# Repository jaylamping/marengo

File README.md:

# Marengo

> **Read first (2026-11-08):** the robot is now **Roark** and its software is being rebuilt as a fresh, lean stack in its own repo, [jaylamping/roark](https://github.com/jaylamping/roark). This repo is the hardware repo and the read-only reference for the legacy software. Start with
> [roark/TENETS.md](https://github.com/jaylamping/roark/blob/main/TENETS.md) and [roark/PLAN.md](https://github.com/jaylamping/roark/blob/main/PLAN.md). The
> tenets override everything below and every ADR. The existing crates (Davout, Berthier, Chappe, robstride, marengo-pi and the
> rest) are **legacy**: don't extend them, fix their tests or copy their patterns; they are deleted once the new stack passes
> (see [RECONCILIATION.md](review/sw-foundation-20261108/RECONCILIATION.md)).

Returning to the project: start with [docs/status.md](docs/status.md) for where things stand (bench checkpoint, open issues, open decisions, next steps), then [docs/roadmap.md](docs/roadmap.md).

One repo for a personal, full-size walking humanoid in the Unitree G1 class (1524 mm, 23 DOF, Robstride actuators): CAD manifests, wiring, URDF, the Rust runtime, and the operator UI. The live hardware today is the right 5-DOF arm on the bench, the deliberate first slice of the full body. SolidWorks and the harness docs define joints, frames, and limits. Control, safety, planning, and the operator UI read that same definition. When the robot changes in CAD, software should change with it.

## Naming

| Name | Role |
|------|------|
| Marengo | The robot (mechanical + electrical design, URDF, runtime) |
| Armée | Rust workspace: shared types, kinematics, crates |
| Chappe | Message bus between processes |
| Berthier | Realtime control |
| Davout | Safety supervision |
| Consul | Web frontend |
| Talleyrand, Fouché | Planner and Jetson vision/LLM: not built; the scaffolds were removed (2026-10-03 crate audit), [ADR 0014](docs/decisions/0014-jetson-perception-semantic-motion.md) holds the design |

Infrastructure crates and bins use `marengo-*` names.

Wire schemas live in [`proto/`](proto/). More context: [docs/architecture.md](docs/architecture.md), [docs/roadmap.md](docs/roadmap.md) (full humanoid milestones), [ADRs](docs/decisions/README.md), and [AGENTS.md](AGENTS.md) (detailed contributor/agent guide).

## Repository layout

```
marengo/
├── Cargo.toml              # Armée workspace root
├── proto/                  # Protobuf wire types
├── cad/                  # SolidWorks tree (local only); manifests tracked for MCP
│   └── manifests/        # MCP conventions + vendor registry (JSON)
├── hardware/             # Electrical, prints, BOM, hardware docs
│   ├── electrical/       # PDB, harness, CAN docs
│   ├── prints/             # STLs + slicer notes
│   ├── bom/                # Master BOM
│   └── docs/               # Kinematics, assembly, hardware ADRs
├── assets/                 # Exported from hardware, used by software
│   ├── urdf/marengo.urdf   # Master URDF (right arm today, from CAD)
│   ├── mjcf/marengo.xml    # MuJoCo model mirroring the URDF
│   └── meshes/             # visual/ + collision/ (not exported yet)
├── crates/                 # Armée libraries (each has a README)
├── bins/                   # Pi runtimes and dev tools
├── consul/                 # Frontend (Vite + React + TS)
├── tools/                  # Pi bench MCP, research MCP, limit sync
├── sim/                    # MuJoCo smoke tests
├── models/                 # ONNX policies (Git LFS; none yet)
├── config/                 # robot.yaml, motors.yaml, control.yaml, homing.yaml
├── docs/                   # Status, roadmap, architecture, safety, ADRs, commissioning, reviews
└── scripts/                # URDF export, deploy helpers
```

ONNX policies use Git LFS when present. See [.gitattributes](.gitattributes). CAD binaries are local-only — [cad/README.md](cad/README.md).

## Software

### Crates (`crates/`)

| Crate | Role |
|-------|------|
| `berthier` | 200 Hz control loop: trajectories, τ_g, position law, fuses |
| `davout` | Safety supervisor and the only path to the motors: reference/enable sequencing, limits, caps, watchdog, joint↔motor transform |
| `robstride` | Robstride CAN driver (MIT, lifecycle, parameters) |
| `chappe` | Topic bus (protobuf envelopes) and Unix-socket IPC |
| `armee-proto` | Generated protobuf types |
| `armee-kinematics` | URDF limits and velocity-scaled envelope |
| `armee-dynamics` | Gravity torques from URDF; calibration fits |
| `marengo-config` | Typed YAML config, atomic profile writes |
| `marengo-store` | SQLite log/session store |
| `marengo-candump` | candump parse, summary, Robstride enrichment |
| `marengo-deploy` | Pi self-update and deployed-version logic |
| `marengo-host-metrics` | Linux host metrics for Chappe |
| `marengo-imu` | BNO085 IMU driver (SHTP over I2C) |
| `marengo-support` | Shared tracing init |
| `sim-harness` | URDF↔MJCF parity and sim test helpers |

Each crate's boundary is documented at the top of its `src/lib.rs`; READMEs exist for the core crates.

### Binaries (`bins/`)

| Binary | Host | Purpose |
|--------|------|---------|
| `marengo-pi` | Raspberry Pi | Control loop, CAN, Chappe, stdin REPL |
| `marengo-gateway` | Raspberry Pi | HTTP + WebTransport for Consul, log store |
| `motor-repl` | Pi (bench) | `status`, `disable`, `set-zero`, `protocol-inspect`, `gravity-preview` |
| `marengo-log-cli` | Pi / dev | Log archive, candump, `firmware-timing`, `gravity-fit` |
| `marengo-limit-sync` | Dev | Apply a Durable Set Limits patch to a local checkout |
| `imu-probe` | Pi | BNO085 quaternion probe |

### Frontend

[consul/](consul/) is the operator UI: live telemetry, the Hardware page (master URDF/YAML, Set Limits, Set Zero, readiness), testing panels and a URDF viewer.

### Tools

[`tools/marengo-pi-mcp`](tools/marengo-pi-mcp/README.md) drives the bench from an editor (deploy, logs, candump, calibration, motion suite, enable soak). `tools/marengo-research-mcp` is a research helper.

## Hardware workflow

1. Design in SolidWorks under the local `cad/` tree on the Windows PC (assemblies: `marengo.SLDASM`, sub-assemblies per limb).
2. Document limits and frames in [hardware/docs/kinematics.md](hardware/docs/kinematics.md).
3. Export URDF and meshes: `./scripts/export-urdf.sh` → `assets/`.
4. Wire and CAN: [hardware/electrical/wiring/](hardware/electrical/wiring/).

Vendor CAD (Robstride, extrusions) lives under the local `cad/vendor/`; [cad/manifests/vendor-assets.json](cad/manifests/vendor-assets.json) tracks it.

## Build

Windows development and local CAD live at `J:\code\marengo`; macOS uses a host checkout of the same repository. Docker runs the full Linux workspace checks. Start with [Windows and macOS development](docs/windows-macos-development.md) and [onboarding](docs/onboarding.md).

```bash
docker compose build dev
just check
```

Native host setup is optional ([docs/dev-setup.md](docs/dev-setup.md)). Rust conventions for contributors and agents: [docs/rust-patterns.md](docs/rust-patterns.md), [AGENTS.md](AGENTS.md).

Deploy: MCP `pi_sync_main` (preferred), or `scripts/deploy-pi.sh` / `just deploy-pi-docker`. systemd units: `scripts/systemd/`.

## CI

GitHub Actions runs `scripts/check.sh` in the dev image, plus `sim`, `vcan` and `build-image` jobs ([.github/workflows/ci.yml](.github/workflows/ci.yml)).

## License

MIT OR Apache-2.0. See [LICENSE-MIT](LICENSE-MIT) and [LICENSE-APACHE](LICENSE-APACHE).

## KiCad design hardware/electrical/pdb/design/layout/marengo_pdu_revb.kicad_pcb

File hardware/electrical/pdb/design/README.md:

# Power board rev A: design sketch

2026-11-06. First design pass after the architecture plan ([`../PLAN.md`](../PLAN.md)). **Sketch, not a schematic.** It picks a
part for every block, does the calculations that size them, fixes the sheet structure and the HP-to-LP signal list, and
places everything to scale ([`FLOORPLAN.png`](FLOORPLAN.png)). Every part number is **verify** until checked against its
current datasheet and stock at JLCPCB or Digi-Key during schematic capture. Tool: KiCad 10 (project stub in
[`../../schematics/marengo_pdu/`](../../schematics/marengo_pdu/)).

Decided inputs: leg-ready ratings, 80 A continuous / 150 A for 100 ms on the main path (Joey 07:28Z); BMS on the board,
high-side; regen to the pack first, clamp as backup (Joey 08:58Z); HP + LP boards plus a Pi power stub, no XT breakouts.

## 1. Boards in rev A

| Board | Size | Stack-up | Content |
| --- | --- | --- | --- |
| HP (high power) | 100 × 95 mm | 4 layers, 2 oz outer and inner (verify the fab's heavy-copper option and price) | pack in, pack sense connector, BMS AFE, shunt, BMS FET banks, charge port, E-stop banks, VMOT bulk, regen clamp, 6 port channels, port fuses and connectors, fast current amps |
| LP (low power) | 100 × 53 mm | 6 layers, 1 oz | supervisor, 2 CAN bridges, USB hub, 6 CAN transceivers, 12 V and 24 V front ends, point-of-load rails, rail switches and meters, I/O |
| Pi power stub | 30 × 20 mm | 2 layers | 12 V → 5.1 V 6 A buck at the Pi |
| Pack sense | 40 × 25 mm | 2 layers | 14 tap fuses, 3 NTC, 2 × 10 Micro-Fit (battery thread spec) |

## 1a. No plugs on the boards: everything leaves on pigtails (frame check 09:16Z)

The frame thread measured the plug room around the carrier (main 733b9d0): 13.6 mm above the HP top edge before the shared
front rail and shelf plate, 8.5 mm in front, the side edges blocked except a 10 mm band at Z 40 to 50, and 35 mm below the LP
bottom edge. No XT plug fits on the HP board. So rev A puts **no high-current connector on either board**:

- **High-current exits are ring-lug pigtails on low-profile threaded board terminals** (Würth REDCUBE-class M4 press-fit or SMT
  terminals, about 5 to 8 mm tall, 80 A class, verify). Serviceable with a screwdriver, no solder joint carrying the current,
  and the cable leaves flat along the board.
- **Pack power and pack sense mate at the back, at the D2 door,** not at the board. The HP top edge carries a 10 AWG pair and the
  sense harness over the pack's top edge (8.6 mm headroom, fine for cable) to the pack's rear top corner, where they meet the
  pack's XT90S and the battery thread's sense board (pack rear face, X 5 to 45, Y 318 to 343). Unplug at the door, slide the
  pack out: no reaching into the torso, and no shelf cutout needed. Battery thread (09:18Z): the pack's XT90S pigtail is about 60 mm of
  10 AWG from the fuse, and both pack-side connectors sit in a printed holder on the case; board-side leads reach that holder with
  about 30 mm of slack.
- **Arm ports:** pigtails from the HP top corners run up the front corners with the trunk; the arm trunk's first XT30(2+2) joint
  becomes an inline connector on that run. Agreed with the trunk thread (09:18Z): about 250 mm of 16 AWG or heavier plus the
  CAN pair, XT30(2+2) **female on the pigtail** (live side), joint at the frame step corner around Y 360 to 380, 80 to 100 mm
  short of the pitch RS03's top-rear flat, reachable through a removable shell panel, 30 mm of slack at the joint.
- **Waist, aux, leg ports and the charge input:** pigtails leave the HP side edges in the open Z 40 to 50 band and drop past
  the LP board to inline connectors below Y 190 (35 mm of room), or straight to the shell charge port. The leg pigtails are
  fitted when the legs exist.
- **LP bottom edge** carries the small connectors (fans, rail outputs, USB, E-stop loop, sensors), mating downward.
- The floorplan's connector boxes now read as terminal pads; the layout gate re-draws them as such.
- Cable paths reserved by the frame thread (main e1be5af, item 27): over-the-pack run X −35 to 30, Y 345 to 353.6; front-corner
  trunks X ±47 to 55, Z 62 to 70; side drops |X| 50 to 55, Z 40 to 50, Y 160 to 300; LV up-run X 33 to 45, Z 50 to 60, Y 340 to 376
  (12 V, USB, CAN, fan leads to the upper bay). **Layout constraint:** HP top-edge ring lugs and the 10 AWG bend stay inside
  Y 340 to 353.6, Z 43.5 to 60, so the terminals sit flat with the lug pointing up and the cable turning rearward over the pack.

## 2. High-power board

### 2.1 Main path parts

| Block | Part (verify) | Qty | Why |
| --- | --- | --- | --- |
| Pack input | 2 × M4 threaded board terminals + 10 AWG ring-lug pigtail to an XT90 at the pack's rear top corner (section 1a) | 1 | the board's rear face sits 3.5 mm off the pack lid, so nothing mounts there |
| Pack sense | low-profile locking board header (JST GH or Micro-Fit vertical, to fit 13.6 mm) + harness to the pack sense board's 2 × 10 at the rear | 1 | 14 taps, 3 NTC, presence loop, spare |
| BMS AFE | TI BQ76952 on the HP board, next to the shunt and FET banks, so the gate drive and Kelvin sense stay short | 1 | 13 cells per datasheet Table 16-3 (cells 1 to 12 on VC0 to VC12, cell 13 on VC15 to VC16, VC13 to VC15 tied to VC12; section 2.2); 3 pack NTCs plus 1 board NTC; DFETOFF from the E-stop loop and the presence loop; I2C to the LP supervisor through the board-to-board connector |
| Charge port | M4 terminals + pigtail to the shell charge port (XT60), reverse-polarity FET, presence divider | 1 | 4 A, CV 53.9 V; joins PACK+ after the BMS FETs (common port) |
| Pack shunt (low side, for the AFE) | 0.25 mΩ 4-terminal, 5 W, 3921 size (Vishay WSLP3921 or Bourns CSS4J-4026 class) | 1 | 80 A → 20 mV, 1.6 W |
| BMS CHG bank, DSG bank (back-to-back) | Infineon IPT015N10N5 (100 V, 1.5 mΩ, TOLL) | 4 + 4 | see 2.2 |
| BMS predischarge FET + resistor | small 100 V P-FET + 100 Ω 3 W | 1 | AFE PDSG pin (datasheet p45: PDSG charges the load, PCHG charges a low battery), charges VSYS bulk before DSG closes |
| E-stop bank A, bank B | IPT015N10N5 | 3 + 3 | single direction, body diodes VMOT → VSYS (PLAN 3.4) |
| E-stop gate drivers | TI TPS4810-Q1 class 100 V smart high-side driver, one per bank, enable from the loop | 2 | hardware path, short-circuit protection built in |
| VMOT bulk | 8 × 220 µF 80 V polymer-hybrid, Ø10 × 12.5 mm, laid flat if needed | 8 | about 1.8 mF, under the 24 mm height |
| VMOT TVS | SMDJ58A class | 2 | fast edges only |
| Regen clamp | comparator + 100 V FET (IPT015N10N5) self-powered from VMOT; external Arcol HS25 10 Ω 25 W aluminium-clad resistor on the front bottom rail, NC thermostat in the E-stop loop | 1 | see 2.3 |

### 2.2 FET bank sizing

- IPT015N10N5: about 1.5 mΩ at 25 °C, about 2.4 mΩ hot (verify). Four in parallel → 0.6 mΩ hot per bank.
- Conduction loss at 80 A continuous: BMS (two banks in series) 2 × 0.6 mΩ × 80² = 7.7 W; E-stop A + B with 3 each
  (0.8 mΩ hot) = 2 × 0.8 mΩ × 80² = 10 W. **At the typical 10 to 30 A it is 0.2 to 1.6 W in total.** 80 A continuous is a
  rating, not a use case; at that level the board needs the fan and the copper pour to spread about 20 W. Thermal check in the
  layout gate.
- Short circuit: the pack can push about 54.6 V / 0.09 Ω ≈ 600 A prospective. AFE SCD at 40 mV on 0.25 mΩ = **160 A, delay set
  to the minimum (about 15 µs, verify)**. In practice the Class T pack fuse, the port eFuses (faster, lower) and the FET pulse
  rating all share this; the schematic gate must show the FET SOA covers 600 A for about 50 µs.
- Superseded at gate 3 by [RATIONALE-log](RATIONALE-log.md) (0.3 mΩ, OCD1 24 mV, OCC 12 mV, SCD 60 mV). AFE thresholds on 0.25 mΩ, corrected against the BQ76952 datasheet SLUSE13B (p22: OCD/OCC in 2 mV steps, OCC delay max
  425 ms): **OCD1 16 mV = 64 A** (hardware comparator, ≤ 425 ms), **OCD3 60 A for 1 s** (current-based, firmware level inside the
  AFE) as the agreed 60 A ceiling, **OCC 12 mV = 48 A at 425 ms** (stays under the P50B's 50 A pack charge limit), **SCD 40 mV =
  160 A** (valid step).
- Cell wiring per datasheet Table 16-3 (p75): cells 1, 2 and 16 must be real, so cells 1 to 12 on VC0 to VC12, cell 13 on
  VC15 to VC16, VC13 to VC15 shorted to VC12 as the table shows. Thermistors: TS1, TS3, CFETOFF and HDQ as thermistor inputs,
  TS2 left free for wake from SHUTDOWN (DFETOFF stays on the E-stop loop).

### 2.3 Regen clamp sizing

- Threshold 56.77 V on, 55.77 V off (1 V hysteresis, gate 3), self-powered from VMOT.
- Resistor 10 Ω: 56.77² / 10 = 322 W while on, 5.7 A, which matches the host's 5 A braking cap when the pack is full (PLAN
  3.4). The HS25 has no published pulse rating (see below); the supervisor logs on-time and the resistor's NTC, and an NC
  thermostat on its plate opens the E-stop loop in hardware.
- Arm drop for scale: about 15 J, under 0.1 s of clamp on-time.

### 2.4 Port channels

| Item | Arms, waist, aux (4) | Legs (2, unpopulated in rev A) |
| --- | --- | --- |
| Hot-swap controller | TI LM5069 (9 to 80 V, circuit breaker, dV/dt soft start) | LM5069 |
| FET | 1 × IPT015N10N5 | 2 × IPT015N10N5 |
| Sense resistor (LM5069, shared with the meter and fast amp) | 2.5 mΩ, 3 W (1.0 W at 20 A) → 22 A limit | 1.2 mΩ, 5 W (1.9 W at 40 A) → 46 A limit |
| Meter | TI INA228 (85 V, 20-bit, energy registers) on the same shunt | INA228 |
| Fast current | TI INA241 (−5 to 110 V common mode) on the same shunt → LP ADC | INA241 |
| Fuse | 15 A blade, **58 V DC rated** (Littelfuse 997 MINI 58 V class) in a 58 V holder | 40 A, 58 V |
| Load-side clamp | 59 V mini clamp, about 20 W (footprint, may stay unpopulated) | same |
| CAN TVS | NUP2105L class at the connector | same |
| Connector | M4 terminals + CAN header on the board; pigtail to an inline XT30(2+2) | M4 terminals + CAN header; pigtail to inline XT60 + JST GH |

> Port values in this table are superseded: arm, waist, aux now use 3 mΩ, limit 16.2 to 20.5 A, software trip 15 A, 20 A fuse. See [RATIONALE-log.md](RATIONALE-log.md), follow-ups.

The LM5069 current limit is set by a 55 mV (typ, verify) sense threshold: 2.5 mΩ gives 22 A for the 20 A ports, 1.2 mΩ gives
46 A for the 40 A legs. The circuit-breaker timer is set so the electronic trip always beats the blade fuse.

## 3. Low-power board

| Block | Part (verify) | Notes |
| --- | --- | --- |
| Supervisor MCU | ST STM32G0B1 (USB, plenty of I2C, low power) | separate from the CAN bridges |
| CAN bridges | 2 × ST STM32G474 (3 FDCAN each), candleLight/gs_usb firmware | 6 buses |
| USB hub | Microchip USB2514B (4 port) | supervisor + 2 bridges + service port; one USB-C up to the Pi |
| CAN | 6 × TI TCAN1462V-Q1, non-isolated (gate 3 default) | bus pins ±58 V, ±45 V differential |
| 12 V intermediate, 150 W | TI LM5145 (6 to 75 V sync buck controller) + 100 V FETs | from VSYS through the ideal diode |
| 24 V, 75 W | second LM5145 | from VSYS |
| Ideal diode + hold-up | TI LM74700-Q1 + 1 mF at VSYS (rides 10 ms at 90 W down to 20 V) | |
| 7.4 V servo (6 to 8.4 V), 5 A | TI TPS56637 (4.5 to 28 V in, 6 A) | adjustable by resistor |
| 5 V peripheral, 4 A | TPS56637 | |
| 3.3 V peripheral, 2 A | TI TPS62933 | |
| 5 V / 3.3 V clean | TI TPS7A20 LDOs | under 5 mV ripple |
| Spare rail slot, 3 A | TPS62933 footprint, output set by resistor | |
| 3.3 V always-on | TI LMR38010 (4.2 to 80 V in, 1 A) | from VSYS, ahead of everything |
| Rail switches | TI TPS2663 (60 V, 6 A eFuse) per 12 V and 24 V output; TPS22965 class for 5 V and 3.3 V | each switchable by the supervisor |
| Rail meters | INA238 per output (10) | 2 I2C buses, 5 meters each |
| Fan drivers | 3 × 4-pin PWM headers, tach to the supervisor | |
| E-stop loop | 12 V loop supply, opto or comparator inputs, 2 independent enable outputs to the HP gate drivers | no firmware in the enable path |

## 4. Schematic sheet structure (KiCad hierarchy)

```
marengo_pdu (root)
├── HP_power_board
│   ├── pack_input_shunt_afe   (BQ76952 lives on HP)
│   ├── bms_fets_precharge
│   ├── estop_banks
│   ├── vmot_bulk_clamp
│   └── port_channel ×6        (one sheet, instanced; legs DNP)
├── LP_logic_board
│   ├── supervisor_mcu
│   ├── can_bridges_usb_hub
│   ├── can_phy ×6             (instanced)
│   ├── front_end_12v_24v
│   ├── pol_rails
│   ├── rail_switches_meters
│   └── io_fans_estop_loop
├── pi_power_stub
└── pack_sense_board
```

## 5. HP-to-LP board-to-board connector (draft)

> Superseded by the captured pinout: two 2x15 ribbons, J101 and J102 on `HP_power_board.kicad_sch`. Reasons are in [RATIONALE-log.md](RATIONALE-log.md), section HP_power_board top sheet.

One locking 2 × 30 header, 2.0 mm pitch, along the HP bottom edge and the LP top edge. No motor current crosses it.

| Pins | Signal |
| --- | --- |
| 6 | VSYS (to the LP front ends, up to 5 A total) |
| 6 | GND |
| 2 | E-stop enable A, enable B (loop logic on LP → gate drivers on HP) |
| 2 | E-stop bank A and B status (drain-source sense) |
| 2 | VMOT sense, clamp status |
| 6 | port enables |
| 6 | fast current outputs from the INA241s |
| 3 | AFE I2C (SDA, SCL) and AFE ALERT |
| 2 | HP meter I2C (port INA228s, HP NTCs) |
| 2 | AFE DFETOFF (loop) and RST_SHUT |
| 12 | CAN_H / CAN_L for the six ports, from the transceivers on LP to the port connectors on HP |
| 2 | charger present, board present |
| 9 | spare and extra GND between CAN pairs |

## 6. Next

1. Joey installs KiCad 10 on Joey-PC.
2. Schematic capture sheet by sheet, starting with the HP main path and the AFE (the safety-critical core), with the calculation
   notes above carried into the schematic as text.
3. Gate 3 review of the schematic (review recipe), then layout.

## 1b. Frame gate 2 constraints for layout (frame thread 11:23Z, main 8a15651)

- **Stack:** carrier Z 37.5 to 41.5, 6 mm M3 F-F standoffs, PCBs from Z 47.5 (top copper Z 49.1), component ceiling Z 61.5. That
  leaves 12.4 mm above the board; the 10.8 mm hold-up caps keep 1.6 mm. Standoff hole positions are set at layout and sent to
  the frame thread.
- **Corner screw heads:** X ±46.5 to 51, Y 175 to 203 and 325 to 353, Z 55 to 65. Boards stay 100 mm wide. Each outer corner
  (|X| > 46, Y 190 to 203 and Y 325 to 340) is a keep-out for parts taller than 5 mm. The arm-port M4 terminals and their
  upward ring lugs move inboard of |X| 44, clear of the posts at Y 325 to 353.
- **Brake resistor, rev A: Arcol HS25 10 Ω** (frame main 04983bb). It replaces the HS50 to clear the pack's bottom front edge.
  Datasheet maxima: 28.0 wide, 51.0 over the tags, 14.6 tall, holes on 18.3 × 19.8 mm. It sits flat on a 2 mm aluminium plate on
  the front bottom rail's inner face, at |X| ≤ 25.5, Y 154 to 182, Z 33.4 to 48. Arcol publishes no pulse rating, so ask Arcol
  before the leg stage; the 2 Ω leg stage takes a bigger part in the 37 mm rail reserve. Leads go to the LP bottom edge.
  Keep the LP bottom-edge connectors at |X| > 36 or above Y 190. BOM and schematic now carry the HS25.
- **Pigtail bundles, per port, flat:**
  - Arm: 2 × 16 AWG silicone (Ø about 2.9) plus a twisted CAN pair (about Ø2.5), about 8 × 3 mm.
  - Leg: 2 × 12 AWG silicone (Ø about 4) plus CAN, about 10.5 × 4 mm.
  - One arm bundle fits the 5 × 8 mm side band. A leg bundle does not fit at the band's full height, and an arm plus a leg
    together never fit in one cross-section.
  - All ring lugs are booted with heat-shrink.
- **Housing bond:** if the RS03 housings are at GND, the frame becomes GND through the motors and the 1 MΩ || 10 nF bond is
  moot. Meter-check a real RS03 (housing to its GND pin) before layout fixes the bond.

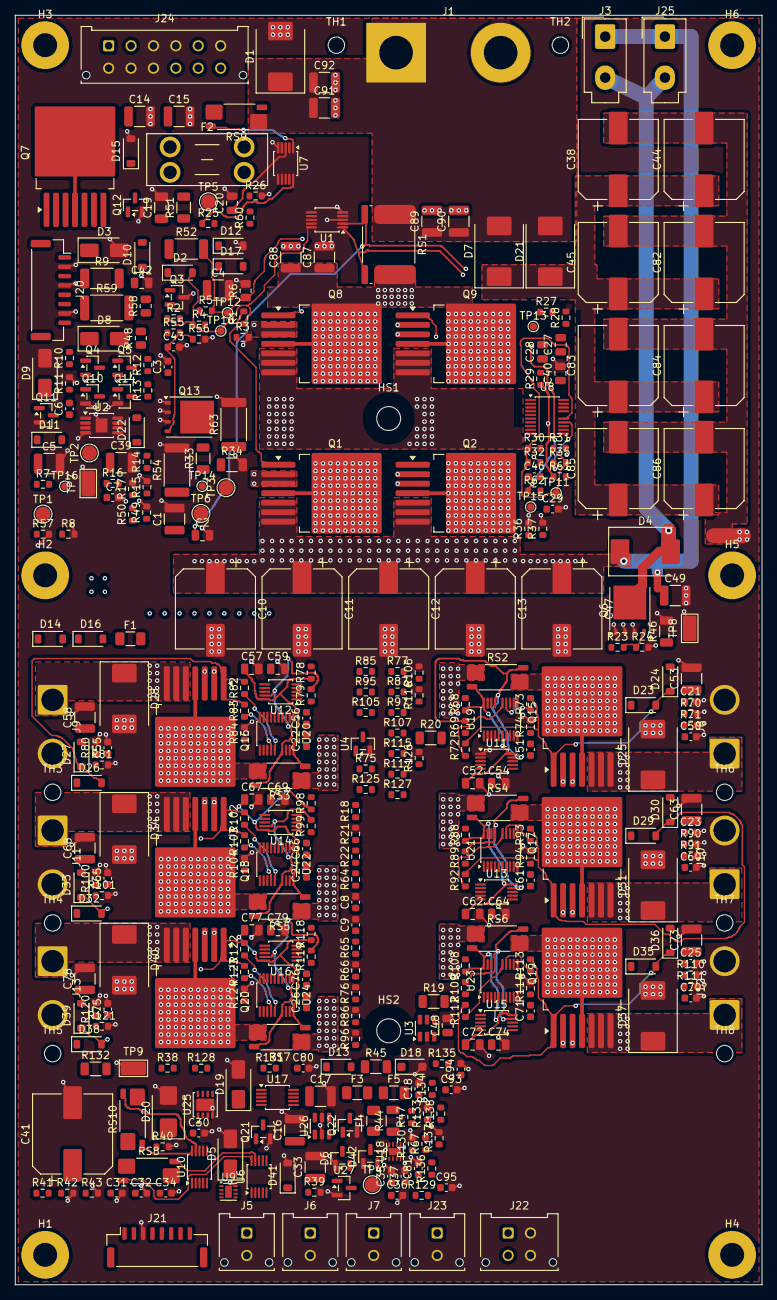
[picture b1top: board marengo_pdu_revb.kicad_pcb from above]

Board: 4 copper layers, 100.0 x 170.0 mm, 387 parts (0 on the bottom side), 201 nets.

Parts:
C1: 1uF 100V X7R soft-term; C_1210_3225Metric
C2, C20: 100nF 100V X7R soft-term; C_0805_2012Metric
C3: 4.7nF C0G; C_0603_1608Metric
C4: 100nF 100V C0G; C_1210_3225Metric
C5: 10uF 50V X7R; C_1210_3225Metric
C6: 2.2nF C0G; C_0603_1608Metric
C7: 10nF 50V X7R; C_0603_1608Metric
C8, C18, C21, C22, C23, C24, C25, C26, C30, C32, C34, C36, C43, C80, C94: 100nF 50V X7R; C_0603_1608Metric
C9: 100pF C0G; C_0603_1608Metric
C10, C11, C12, C13, C38, C44, C45, C47, C82, C83, C84, C85, C86: 47uF 80V EEH-ZC1K470P; CP_Elec_10x10.5
C14, C15, C53, C58, C63, C68, C73, C78: 2.2uF 100V X7R; C_1210_3225Metric
C16, C17, C33: 22uF 25V X7R; C_1210_3225Metric
C19: 220nF C0G; C_1206_3216Metric
C27, C52, C54, C57, C59, C62, C64, C67, C69, C72, C74, C77, C79: 100nF 100V X7R; C_0805_2012Metric
C28: 2.2uF 25V X7R; C_0805_2012Metric
C29: 680pF C0G; C_0603_1608Metric
C31, C35, C81: 3.3nF C0G; C_0603_1608Metric
C37, C95: 1nF 50V X7R; C_0603_1608Metric
C39, C49: 1uF 100V X7R; C_1210_3225Metric
C40: 22nF 100V; C_0805_2012Metric
C41: 330uF 25V EEH-ZA1E331P; CP_Elec_10x10.5
C42: 1uF 50V X7R; C_0805_2012Metric
C46: 1nF C0G; C_0603_1608Metric
C48: 4.7uF 10V X7R; C_0805_2012Metric
C50, C55, C60, C65, C70, C75: 1uF 16V X7R; C_0603_1608Metric
C51, C56, C61, C66, C71, C76, C93: 220nF 25V X7R; C_0603_1608Metric
C87, C88, C89, C90, C91, C92: 4.7uF 100V X7R; C_1210_3225Metric
D1: 5.0SMDJ58A; D_SMC
D2, D10, D11, D22, D23, D26, D29, D32, D35, D38: BAV19W; D_SOD-123
D3, D9: SMAJ15A; D_SMA
D4: MBRS3100T3G; D_SMC
D5, D19: B340A-13-F; D_SMA
D6, D42: BAT54S; SOT-23
D7, D21, D25, D28, D31, D34, D37, D40: SK810L-TP; D_SMC
D8: ES1D; D_SMA
D12, D15: BZT52C12; D_SOD-123
D13, D17: BAT46W; D_SOD-123
D14: BZT52C10; D_SOD-123
D16: BZT52C5V1; D_SOD-123
D18: BZT52H-C68,115; D_SOD-123F
D20: SMBJ15A; D_SMB
D24, D27, D30, D33, D36, D39: BZT52C15; D_SOD-123
D41: BZT52C3V3; D_SOD-123
F1: 250mA 125V 0466.250; Fuse_1206_3216Metric
F2: 20A 58V MINI 0997020.WXN; Fuseholder_Blade_Mini_Keystone_3568
F3, F4: 5A 32V 0466005; Fuse_1206_3216Metric
F5: 2A 32V 0466002; Fuse_1206_3216Metric
H1, H2, H3, H4, H5, H6: MountingHole_3.2mm_M3_Pad
HS1, HS2: MountingHole_3.2mm_M3
J1: Pack: 8 AWG pigtail pair to an XT90 (mat; SolderWire-8AWG_1x02_P14mm_D4.5mm_OD8mm
J3: HS50 A (+X): 1 VBUS, 2 FET drain (Mini-F; Molex_Mini-Fit_Jr_5566-02A_2x01_P4.20mm_Vertical
J5: 12 V to Jetson (fused, block 10c); Molex_Micro-Fit_3.0_43045-0212_2x01_P3.00mm_Vertical
J6: 12 V to Pi 5 V buck (fused, block 10c); Molex_Micro-Fit_3.0_43045-0212_2x01_P3.00mm_Vertical
J7: 12 V to fans (fused, block 10c); Molex_Micro-Fit_3.0_43045-0212_2x01_P3.00mm_Vertical
J8: L arm: 16 AWG pigtail pair, 1 +, 2 retur; SolderWire-2.5sqmm_1x02_P7.2mm_D2.4mm_OD3.6mm
J9: R arm: 16 AWG pigtail pair, 1 +, 2 retur; SolderWire-2.5sqmm_1x02_P7.2mm_D2.4mm_OD3.6mm
J10: waist: 16 AWG pigtail pair, 1 +, 2 retur; SolderWire-2.5sqmm_1x02_P7.2mm_D2.4mm_OD3.6mm
J11: aux: 16 AWG pigtail pair, 1 +, 2 return; SolderWire-2.5sqmm_1x02_P7.2mm_D2.4mm_OD3.6mm
J12: L leg: 14 AWG pigtail pair, 1 +, 2 retur; SolderWire-2.5sqmm_1x02_P7.2mm_D2.4mm_OD3.6mm
J13: R leg: 14 AWG pigtail pair, 1 +, 2 retur; SolderWire-2.5sqmm_1x02_P7.2mm_D2.4mm_OD3.6mm
J20: E-stop: 1 NC out, 2 GND, 3 NC return, 4; JST_GH_SM08B-GHS-TB_1x08-1MP_P1.25mm_Horizontal
J21: Pi: 3V3, SDA, GND, SCL, E-stop pressed (; JST_GH_SM08B-GHS-TB_1x08-1MP_P1.25mm_Horizontal
J22: SPARE_SW, off with the motors (2 x 2, ke; Molex_Micro-Fit_3.0_43045-0412_2x02_P3.00mm_Vertical
J23: SPARE_ON, always on; Molex_Micro-Fit_3.0_43045-0212_2x01_P3.00mm_Vertical
J24: 12 V converter pigtail: 1-2 +VIN, 3-4 -V; Molex_Micro-Fit_3.0_43045-1212_2x06_P3.00mm_Vertical
J25: HS50 B (-X): 1 VBUS, 2 FET drain (Mini-F; Molex_Mini-Fit_Jr_5566-02A_2x01_P4.20mm_Vertical
Q1, Q2, Q7, Q8, Q9, Q15, Q16, Q17, Q18, Q19, Q20: IPB017N10N5LFATMA1; TO-263-7_TabPin4
Q3: MMBTA92LT1G; SOT-23
Q4: MMBT3906; SOT-23
Q5, Q10, Q11, Q14, Q21: MMBT3904; SOT-23
Q6, Q13: BSC040N10NS5ATMA1; TDSON-8-1
Q12, Q22: 2N7002; SOT-23
R1, R2, R23, R25, R31, R32: 10R; R_0603_1608Metric
R3: 34k 1%; R_0603_1608Metric
R4, R12, R66: 1k; R_0603_1608Metric
R5, R75, R85, R95, R105, R115, R125, R131: 22k; R_0603_1608Metric
R6: 33k; R_0805_2012Metric
R7: 464k; R_0603_1608Metric
R8: 49.9k; R_0603_1608Metric
R9: 680R 0.5W; R_2010_5025Metric
R10: 4.7k; R_0603_1608Metric
R11, R14, R16, R17, R27, R67, R76, R86, R96, R106, R116, R126, R129: 10k; R_0603_1608Metric
R13, R24, R28, R37, R38, R41, R50, R55, R65, R71, R72, R77, R81, R82, R87, R91, R92, R97, R101, R102, R107, R111, R112, R117, R121, R122, R127, R130, R137: 100k; R_0603_1608Metric
R15: 1.2k; R_0603_1608Metric
R18, R134: 9.09k; R_0603_1608Metric
R19: 499k 0.1%; R_1206_3216Metric
R20: 604k 0.1%; R_1206_3216Metric
R21: 51.1k 0.1%; R_0603_1608Metric
R22, R64: 9.53M; R_0603_1608Metric
R26: 37.4k 1%; R_0603_1608Metric
R29, R68, R78, R88, R98, R108, R118, R138: 100R; R_0603_1608Metric
R30, R56: 1M; R_0603_1608Metric
R33, R34: 47k 1%; R_1206_3216Metric
R35, R73, R83, R93, R103, R113, R123: 22R; R_0603_1608Metric
R36: 40.2k 1%; R_0603_1608Metric
R39: 68k; R_0603_1608Metric
R40: 499R 1%; R_0603_1608Metric
R42, R47: 33k; R_0603_1608Metric
R43: 1.02k 1%; R_0603_1608Metric
R44: 3.3k; R_1206_3216Metric
R45, R46: 100k; R_1206_3216Metric
R48: 220k; R_0805_2012Metric
R49, R57: 220k; R_0603_1608Metric
R51: 470k; R_1206_3216Metric
R52: 10k 0.75W; R_2010_5025Metric
R53: copper link; NetTie-2_SMD_Pad2.0mm
R54: 2R 2512 pulse-rated 100mJ; R_2512_6332Metric
R58: 47k; R_0805_2012Metric
R59: 22R CRCW251222R0FKEGHP; R_2512_6332Metric
R60: 220R; R_0603_1608Metric
R61, R62: 0R; R_0603_1608Metric
R63: 4.7k 2W; R_2512_6332Metric
R69, R79, R89, R99, R109, R119: 4.64k 1%; R_0603_1608Metric
R70, R80, R90, R100, R110, R120: 20k 1%; R_0603_1608Metric
R74, R84, R94, R104, R114, R124: 10M; R_0603_1608Metric
R128: 2.2k; R_0603_1608Metric
R132: 118k 1%; R_1206_3216Metric
R133, R135: 10k 1%; R_0603_1608Metric
R136: 499k 1%; R_0603_1608Metric
RS1: 0.5mR Bourns CSS4J-4026R-L500F 5W; R_Shunt_Isabellenhuette_BVR4026
RS2, RS3, RS4, RS5, RS6, RS7: 2mR 2512 CSS2H-2512K-2L00F 5W; R_Shunt_Vishay_WSK2512_6332Metric_T1.19mm
RS8: 2mR 2512 Kelvin WSK25122L000FEA; R_Shunt_Vishay_WSK2512_6332Metric_T1.19mm
RS9, RS10: 5mR 2512 Kelvin WSK25125L000FEA; R_Shunt_Vishay_WSK2512_6332Metric_T1.19mm
TH1, TH2, TH3, TH4, TH5, TH6, TH7, TH8: MountingHole_2.2mm_M2
TP1: TP VCTL; TestPoint_Pad_D2.0mm
TP2: TP RUN; TestPoint_Pad_D2.0mm
TP3: TP VBUS; TestPoint_Pad_D2.0mm
TP4: TP +12V; TestPoint_Pad_D2.0mm
TP5: TP BRK_IN; TestPoint_Pad_D2.0mm
TP6: TP MID; TestPoint_Pad_D2.0mm
TP7, TP8, TP9: TP GND; TestPoint_Keystone_5015_Micro_Mini
TP10: TP GATE; TestPoint_Pad_D1.0mm
TP11: TP GATE_A; TestPoint_Pad_D1.0mm
TP12: TP UVLO; TestPoint_Pad_D1.0mm
TP13: TP FLT_A; TestPoint_Pad_D1.0mm
TP14: TP SW_D; TestPoint_Pad_D1.0mm
TP15: TP ABS; TestPoint_Pad_D1.0mm
TP16: TP WDO_N; TestPoint_Pad_D1.0mm
U1: LM5069MMX-1; MSOP-10_3x3mm_P0.5mm
U2: TPS7A4001DGNR; HVSSOP-8-1EP_3x3mm_P0.65mm_EP1.57x1.89mm
U3, U26: TLV1805DBVR; SOT-23-6
U4, U27: LM4040AIM3-2.5; SOT-23
U6, U10, U11, U12, U13, U14, U15, U16, U17: INA237AIDGSR; TSSOP-10_3x3mm_P0.5mm
U7: LM5069MMX-2; MSOP-10_3x3mm_P0.5mm
U8: TPS48100QDGXRQ1; TPS48100_DGX_VSSOP-19
U9, U18: TPS259541DSGR; Texas_DSG0008A_WSON-8-1EP_2x2mm_P0.5mm_EP0.9x1.6mm
U19, U20, U21, U22, U23, U24: TPS48111LQDGXRQ1; TPS48100_DGX_VSSOP-19
U25: TPS3431SDRBR; VSON-8-1EP_3x3mm_P0.65mm_EP1.65x2.4mm

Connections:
/+3V3_PI: C18.1, C21.1, C22.1, C23.1, C24.1, C25.1, C26.1, C30.1, C34.1, D6.2, D13.2, D42.2, J21.1, R67.2, U6.2, U6.6, U10.1, U10.6, U11.6, U12.2, U12.6, U13.6, U14.6, U15.1, U15.6, U16.1, U16.2, U16.6, U17.6
/+12V: C32.1, C36.1, C41.1, D20.1, F3.1, F4.1, F5.1, R41.1, RS8.4, TP4.1, U6.8, U9.3, U9.4, U18.3, U18.4
/+12V_FAN: F5.2, J7.1
/+12V_JET: F3.2, J5.1
/+12V_PI: F4.2, J6.1
/+12V_RAW: C16.1, C17.1, J24.10, J24.11, J24.12, RS8.1
/ABS: C38.1, C44.1, C45.1, C82.1, C83.1, C84.1, C85.1, C86.1, D7.1, D21.1, R46.1, TP15.1
/ABS_N: C38.2, C44.2, C45.2, C82.2, C83.2, C84.2, C85.2, C86.2, Q13.5, R53.1, R54.1
/BAT: C1.1, C89.1, C90.1, C91.1, C92.1, D1.1, D7.2, D21.2, F1.1, J1.1, RS1.1, RS9.1
/BAT_CTL: C39.1, D8.1, U2.5, U2.8
/BAT_F: F1.2, R59.1
/BAT_R: D8.2, R59.2
/BRK_D: Q7.4, RS9.4
/BRK_F: F2.2, J24.1, J24.2
/BRK_G1: Q7.1, R25.2
/BRK_GATE: R25.1, U7.10
/BRK_IN: C14.1, C15.1, F2.1, Q7.2, Q7.3, Q7.5, Q7.6, Q7.7, R51.1, R132.1, TP5.1, U7.9
/BRK_ON: J24.5, R60.2
/BRK_OND: Q12.3, R60.1
/BRK_P: R26.1, U7.7
/BRK_PG: D15.1, Q12.1, R51.2, U7.8
/BRK_T: C19.1, U7.6
/BST_A: C28.1, U8.12
/BST_L1: C51.1, U19.12
/BST_L2: C56.1, U20.12
/BST_L3: C61.1, U21.12
/BST_L4: C66.1, U22.12
/BST_L5: C71.1, U23.12
/BST_L6: C76.1, U24.12
/CDV: C4.1, D2.1, Q3.2
/CDV_B: Q3.1, R4.2
/CL_D: D4.2, J3.2, J25.2, Q6.5
/CL_DIV: R19.2, R20.1
/CL_G: Q6.4, R23.2, R24.1
/CL_HY: R22.2, R64.1
/CL_OUT: R22.1, R23.1, R65.1, U3.1
/CL_SENSE: C9.1, R20.2, R21.1, R64.2, U3.4
/CL_TM: C48.1, R65.2, R66.1, U17.10
/CSN_A: C46.2, R62.2, U8.17
/CSP_A: C46.1, R61.2, U8.18
/CSP_L1: R68.2, U19.18
/CSP_L2: R78.2, U20.18
/CSP_L3: R88.2, U21.18
/CSP_L4: R98.2, U22.18
/CSP_L5: R108.2, U23.18
/CSP_L6: R118.2, U24.18
/CWD: C81.1, U25.2
/D_L1: C53.1, Q15.4, RS2.4
/D_L2: C58.1, Q16.4, RS3.4, U12.8
/D_L3: C63.1, Q17.4, RS4.4
/D_L4: C68.1, Q18.4, RS5.4
/D_L5: C73.1, Q19.4, RS6.4
/D_L6: C78.1, Q20.4, RS7.4
/EN_A: R27.2, R28.1, U8.1, U8.3
/EN_L1: R75.2, R76.1, U19.1
/EN_L2: R85.2, R86.1, U20.1
/EN_L3: R95.2, R96.1, U21.1
/EN_L4: R105.2, R106.1, U22.1
/EN_L5: R115.2, R116.1, U23.1
/EN_L6: R125.2, R126.1, U24.1
/ESTOP_NO: J20.8, R44.2, R45.1
/ESTOP_PI_N: C37.1, D6.3, J21.5, R45.2
/FB_CTL: R7.2, R8.1, U2.2
/FLT_A: D12.1, D17.1, TP13.1, U8.5
/FLT_D: D17.2, R52.1
/G1: Q1.1, R1.2
/G1PD_A: R35.1, U8.14
/G2: Q2.1, R2.2
/GA1: Q8.1, R31.2
/GA2: Q9.1, R32.2
/GATE: D2.2, R1.1, R2.1, R4.1, TP10.1, U1.10
/GATE_A: R30.1, R31.1, R32.1, R35.2, TP11.1, U8.15
/GC_L1: C54.1, D23.1, R74.1
/GC_L2: C59.1, D26.1, R84.1
/GC_L3: C64.1, D29.1, R94.1
/GC_L4: C69.1, D32.1, R104.1
/GC_L5: C74.1, D35.1, R114.1
/GC_L6: C79.1, D38.1, R124.1
/GPD_L1: R73.1, U19.14
/GPD_L2: R83.1, U20.14
/GPD_L3: R93.1, U21.14
/GPD_L4: R103.1, U22.14
/GPD_L5: R113.1, U23.14
/GPD_L6: R123.1, U24.14
/GPU_L1: R72.1, U19.15
/GPU_L2: R82.1, U20.15
/GPU_L3: R92.1, U21.15
/GPU_L4: R102.1, U22.15
/GPU_L5: R112.1, U23.15
/GPU_L6: R122.1, U24.15
/G_L1: D23.2, D24.1, Q15.1, R72.2, R73.2
/G_L2: D26.2, D27.1, Q16.1, R82.2, R83.2
/G_L3: D29.2, D30.1, Q17.1, R92.2, R93.2
/G_L4: D32.2, D33.1, Q18.1, R102.2, R103.2
/G_L5: D35.2, D36.1, Q19.1, R112.2, R113.2
/G_L6: D38.2, D39.1, Q20.1, R122.2, R123.2
/I2C_SCL: J21.4, U6.1, U6.5, U10.2, U10.5, U11.5, U12.5, U13.1, U13.5, U14.2, U14.5, U15.5, U16.5, U17.1, U17.2, U17.5
/I2C_SDA: J21.2, U6.4, U10.4, U11.4, U12.4, U13.4, U14.4, U15.4, U16.4, U17.4
/INP_L1: R77.2, U19.3
/INP_L2: R87.2, U20.3
/INP_L3: R97.2, U21.3
/INP_L4: R107.2, U22.3
/INP_L5: R117.2, U23.3
/INP_L6: R127.2, U24.3
/INT_B: Q10.1, Q11.3, R50.2
/ISCP_A: R36.1, U8.8
/ISCP_L1: R69.1, U19.19
/ISCP_L2: R79.1, U20.19
/ISCP_L3: R89.1, U21.19
/ISCP_L4: R99.1, U22.19
/ISCP_L5: R109.1, U23.19
/ISCP_L6: R119.1, U24.19
/IWRN_L1: R70.1, U19.8
/IWRN_L2: R80.1, U20.8
/IWRN_L3: R90.1, U21.8
/IWRN_L4: R100.1, U22.8
/IWRN_L5: R110.1, U23.8
/IWRN_L6: R120.1, U24.8
/LOOP_OUT: J20.1, R9.2
/LOOP_RET: D3.1, J20.3, Q4.2, R13.1
/L_B: C7.1, Q5.1, R12.2, R16.2, R17.1
/L_E: Q5.2, Q21.3
/L_PB: Q4.1, R13.2, R14.1
/L_PC: Q5.3, R14.2
/MID: C28.2, C40.1, D14.1, Q1.4, Q2.4, Q8.2, Q8.3, Q8.5, Q8.6, Q8.7, Q9.2, Q9.3, Q9.5, Q9.6, Q9.7, R30.2, R33.2, R34.1, R47.1, TP6.1, U8.13
/MID_B: Q11.1, R48.2, R49.1
/MID_S: D18.1, R47.2, U17.8
/MID_Z: D14.2, R48.1
/NO_PU: D13.1, R44.1
/PF_D: Q22.3, R138.1
/PF_OUT: Q22.1, R136.1, R137.1, U26.1
/PF_REF: R135.2, R136.2, U26.4
/PF_SENSE: C93.1, R132.2, R133.1, U26.3
/PF_VR: R134.2, R135.1, U27.1
/PORT_FLT_N: J21.7, R67.1, U19.5, U20.5, U21.5, U22.5, U23.5, U24.5
/PRE_G: C43.1, Q13.4, R55.2, R56.1
/PWR: R3.1, U1.7
/PWR_FAIL_N: C95.1, D42.3, J21.8, R138.2
/RST_C: C6.2, R12.1
/RST_IN: C6.1, J20.6, R11.1
/RST_SRC: C42.1, J20.5, Q10.3, Q14.3, R10.2
/RUN: D10.2, D11.2, D22.2, Q4.3, R15.1, R16.1, R38.1, TP2.1
/RUN_A: D11.1, R27.1
/RUN_B: D10.1, R5.1
/RUN_P: D22.1, R75.1, R77.1, R85.1, R87.1, R95.1, R97.1, R105.1, R107.1, R115.1, R117.1, R125.1, R127.1
/SH9_N: RS9.3, U7.1
/SH9_P: C20.1, RS9.2, U7.2, U7.3
/SH12_N: RS8.3, U6.9
/SH12_P: RS8.2, U6.10
/SHL1_N: R69.2, RS2.3, U11.9, U19.17
/SHL1_P: C52.1, R68.1, RS2.2, U11.10, U19.20
/SHL2_N: R79.2, RS3.3, U12.9, U20.17
/SHL2_P: C57.1, R78.1, RS3.2, U12.10, U20.20
/SHL3_N: R89.2, RS4.3, U13.9, U21.17
/SHL3_P: C62.1, R88.1, RS4.2, U13.10, U21.20
/SHL4_N: R99.2, RS5.3, U14.9, U22.17
/SHL4_P: C67.1, R98.1, RS5.2, U14.10, U22.20
/SHL5_N: R109.2, RS6.3, U15.9, U23.17
/SHL5_P: C72.1, R108.1, RS6.2, U15.10, U23.20
/SHL6_N: R119.2, RS7.3, U16.9, U24.17
/SHL6_P: C77.1, R118.1, RS7.2, U16.10, U24.20
/SHSP_N: RS10.3, U10.9
/SHSP_P: RS10.2, U10.10
/SH_N: R62.1, RS1.3, U1.1
/SH_P: C2.1, R29.1, R61.1, RS1.2, U1.2
/SPARE_ON: D19.1, J23.1, U18.5
/SPARE_SW: J22.1, J22.3, RS10.4, U10.8
/SPON_DV: C35.1, U18.1
/SPON_EN: R41.2, R42.1, U18.2
/SPON_ILM: R43.1, U18.7
/SP_DV: C31.1, U9.1
/SP_EN: R38.2, R39.1, U9.2
/SP_ILM: R40.1, U9.7
/SP_SW1: C33.1, D5.1, RS10.1, U9.5
/SW_D: C87.1, C88.1, Q8.4, Q9.4, R33.1, RS1.4, TP14.1
/TIMER: C3.1, U1.6
/TMR_A: C29.1, R37.1, U8.9
/TMR_L1: C50.1, R71.1, U19.9
/TMR_L2: C55.1, R81.1, U20.9
/TMR_L3: C60.1, R91.1, U21.9
/TMR_L4: C65.1, R101.1, U22.9
/TMR_L5: C70.1, R111.1, U23.9
/TMR_L6: C75.1, R121.1, U24.9
/UVLO: R5.2, R6.1, R52.2, TP12.1, U1.3
/VBUS: C10.1, C11.1, C12.1, C13.1, C47.1, C49.1, D4.1, D16.1, J3.1, J25.1, Q1.2, Q1.3, Q1.5, Q1.6, Q1.7, Q2.2, Q2.3, Q2.5, Q2.6, Q2.7, R19.1, R63.1, RS2.1, RS3.1, RS4.1, RS5.1, RS6.1, RS7.1, TP3.1, U1.9
/VB_B: Q14.1, R57.1, R58.2
/VB_Z: D16.2, R58.1
/VCTL: C5.1, C8.1, C94.1, D9.1, R7.1, R9.1, R10.1, R18.1, R50.1, R55.1, R128.1, R134.1, TP1.1, U2.1, U3.6, U26.6
/VREF_CL: R18.2, U3.3, U4.1
/VS_A: C27.1, R29.2, U8.20
/VWD: C80.1, D41.1, R128.2, R131.1, U25.1, U25.3, U25.5
/V_L1: C51.2, D24.2, D25.1, J8.1, Q15.2, Q15.3, Q15.5, Q15.6, Q15.7, U11.8, U19.13
/V_L2: C56.2, D27.2, D28.1, J9.1, Q16.2, Q16.3, Q16.5, Q16.6, Q16.7, U20.13
/V_L3: C61.2, D30.2, D31.1, J10.1, Q17.2, Q17.3, Q17.5, Q17.6, Q17.7, U13.8, U21.13
/V_L4: C66.2, D33.2, D34.1, J11.1, Q18.2, Q18.3, Q18.5, Q18.6, Q18.7, U14.8, U22.13
/V_L5: C71.2, D36.2, D37.1, J12.1, Q19.2, Q19.3, Q19.5, Q19.6, Q19.7, U15.8, U23.13
/V_L6: C76.2, D39.2, D40.1, J13.1, Q20.2, Q20.3, Q20.5, Q20.6, Q20.7, U16.8, U24.13
/WDI: R129.2, R130.1, U25.6
/WDO_N: Q21.1, R131.2, TP16.1, U25.7
/WD_FEED: J21.6, R129.1
GND: C1.2, C2.2, C3.2, C4.2, C5.2, C7.2, C8.2, C9.2, C10.2, C11.2, C12.2, C13.2, C14.2, C15.2, C16.2, C17.2, C18.2, C19.2, C20.2, C21.2, C22.2, C23.2, C24.2, C25.2, C26.2, C27.2, C29.2, C30.2, C31.2, C32.2, C33.2, C34.2, C35.2, C36.2, C37.2, C39.2, C40.2, C41.2, C42.2, C43.2, C47.2, C48.2, C49.2, C50.2, C52.2, C53.2, C54.2, C55.2, C57.2, C58.2, C59.2, C60.2, C62.2, C63.2, C64.2, C65.2, C67.2, C68.2, C69.2, C70.2, C72.2, C73.2, C74.2, C75.2, C77.2, C78.2, C79.2, C80.2, C81.2, C87.2, C88.2, C89.2, C90.2, C91.2, C92.2, C93.2, C94.2, C95.2, D1.2, D3.2, D5.2, D6.1, D9.2, D12.2, D15.2, D18.2, D19.2, D20.2, D25.2, D28.2, D31.2, D34.2, D37.2, D40.2, D41.2, D42.1, J1.2, J5.2, J6.2, J7.2, J8.2, J9.2, J10.2, J11.2, J12.2, J13.2, J20.2, J20.4, J20.7, J21.3, J22.2, J22.4, J23.2, J24.3, J24.4, J24.6, J24.7, J24.8, J24.9, Q3.3, Q6.1, Q6.2, Q6.3, Q10.2, Q11.2, Q12.2, Q13.1, Q13.2, Q13.3, Q14.2, Q21.2, Q22.2, R3.2, R6.2, R8.2, R11.2, R15.2, R17.2, R21.2, R24.2, R26.2, R28.2, R34.2, R36.2, R37.2, R39.2, R40.2, R42.2, R43.2, R46.2, R49.2, R53.2, R54.2, R56.2, R57.2, R63.2, R66.2, R70.2, R71.2, R74.2, R76.2, R80.2, R81.2, R84.2, R86.2, R90.2, R91.2, R94.2, R96.2, R100.2, R101.2, R104.2, R106.2, R110.2, R111.2, R114.2, R116.2, R120.2, R121.2, R124.2, R126.2, R130.2, R133.2, R137.2, TP7.1, TP8.1, TP9.1, U1.4, U1.5, U2.4, U2.9, U3.2, U3.5, U4.2, U6.7, U7.4, U7.5, U8.2, U8.6, U8.7, U8.10, U9.8, U9.9, U10.7, U11.1, U11.2, U11.7, U12.1, U12.7, U13.2, U13.7, U14.1, U14.7, U15.2, U15.7, U16.7, U17.7, U17.9, U18.8, U18.9, U19.2, U19.6, U19.7, U19.10, U20.2, U20.6, U20.7, U20.10, U21.2, U21.6, U21.7, U21.10, U22.2, U22.6, U22.7, U22.10, U23.2, U23.6, U23.7, U23.10, U24.2, U24.6, U24.7, U24.10, U25.4, U25.9, U26.2, U26.5, U27.2

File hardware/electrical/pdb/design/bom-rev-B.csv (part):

"Refs","Value","Footprint","Qty","DNP"
"C1","1uF 100V X7R soft-term","Capacitor_SMD:C_1210_3225Metric","1",""
"C2,C20","100nF 100V X7R soft-term","Capacitor_SMD:C_0805_2012Metric","2",""
"C3","4.7nF C0G","Capacitor_SMD:C_0603_1608Metric","1",""
"C4","100nF 100V C0G","Capacitor_SMD:C_1210_3225Metric","1",""
"C5","10uF 50V X7R","Capacitor_SMD:C_1210_3225Metric","1",""
"C6","2.2nF C0G","Capacitor_SMD:C_0603_1608Metric","1",""
"C7","10nF 50V X7R","Capacitor_SMD:C_0603_1608Metric","1",""
"C8,C18,C21,C22,C23,C30,C32,C34,C36,C80,C94","100nF 50V X7R","Capacitor_SMD:C_0603_1608Metric","11",""
"C9","100pF C0G","Capacitor_SMD:C_0603_1608Metric","1",""
"C10,C11,C12,C13,C38,C44,C45,C47,C82,C83,C84,C85,C86","47uF 80V EEH-ZC1K470P","Capacitor_SMD:CP_Elec_10x10.5","13",""
"C14,C15,C53,C58,C63","2.2uF 100V X7R","Capacitor_SMD:C_1210_3225Metric","5",""
"C16,C17,C33","22uF 25V X7R","Capacitor_SMD:C_1210_3225Metric","3",""
"C19","220nF C0G","Capacitor_SMD:C_1206_3216Metric","1",""
"C24,C25,C26,C43","100nF 50V X7R","Capacitor_SMD:C_0603_1608Metric","4","DNP"
"C27,C52,C54,C57,C59,C62,C64","100nF 100V X7R","Capacitor_SMD:C_0805_2012Metric","7",""
"C28","2.2uF 25V X7R","Capacitor_SMD:C_0805_2012Metric","1",""
"C29","680pF C0G","Capacitor_SMD:C_0603_1608Metric","1","DNP"
"C31,C35,C81","3.3nF C0G","Capacitor_SMD:C_0603_1608Metric","3",""
"C37,C95","1nF 50V X7R","Capacitor_SMD:C_0603_1608Metric","2",""
"C39,C49","1uF 100V X7R","Capacitor_SMD:C_1210_3225Metric","2",""
"C40","22nF 100V","Capacitor_SMD:C_0805_2012Metric","1",""
"C41","330uF 25V EEH-ZA1E331P","Capacitor_SMD:CP_Elec_10x10.5","1",""
"C42","1uF 50V X7R","Capacitor_SMD:C_0805_2012Metric","1",""
"C46","1nF C0G","Capacitor_SMD:C_0603_1608Metric","1","DNP"
"C48","4.7uF 10V X7R","Capacitor_SMD:C_0805_2012Metric","1",""
"C50,C55,C60","1uF 16V X7R","Capacitor_SMD:C_0603_1608Metric","3",""
"C51,C56,C61,C93","220nF 25V X7R","Capacitor_SMD:C_0603_1608Metric","4",""
"C65,C70,C75","1uF 16V X7R","Capacitor_SMD:C_0603_1608Metric","3","DNP"
"C66,C71,C76","220nF 25V X7R","Capacitor_SMD:C_0603_1608Metric","3","DNP"
"C67,C69,C72,C74,C77,C79","100nF 100V X7R","Capacitor_SMD:C_0805_2012Metric","6","DNP"
"C68,C73,C78","2.2uF 100V X7R","Capacitor_SMD:C_1210_3225Metric","3","DNP"
"C87,C88,C89,C90,C91,C92","4.7uF 100V X7R","Capacitor_SMD:C_1210_3225Metric","6",""
"D1","5.0SMDJ58A","Diode_SMD:D_SMC","1",""
"D2,D10,D11,D22,D23,D26,D29","BAV19W","Diode_SMD:D_SOD-123","7",""
"D3,D9","SMAJ15A","Diode_SMD:D_SMA","2",""
"D4","MBRS3100T3G","Diode_SMD:D_SMC","1",""
"D5,D19","B340A-13-F","Diode_SMD:D_SMA","2",""
"D6,D42","BAT54S","Package_TO_SOT_SMD:SOT-23","2",""
"D7,D21,D25,D28,D31","SK810L-TP","Diode_SMD:D_SMC","5",""
"D8","ES1D","Diode_SMD:D_SMA","1",""
"D12,D15","BZT52C12","Diode_SMD:D_SOD-123","2",""
"D13,D17","BAT46W","Diode_SMD:D_SOD-123","2",""
"D14","BZT52C10","Diode_SMD:D_SOD-123","1",""
"D16","BZT52C5V1","Diode_SMD:D_SOD-123","1",""
"D18","BZT52H-C68,115","Diode_SMD:D_SOD-123F","1",""
"D20","SMBJ15A","Diode_SMD:D_SMB","1",""
"D24,D27,D30","BZT52C15","Diode_SMD:D_SOD-123","3",""
"D32,D35,D38","BAV19W","Diode_SMD:D_SOD-123","3","DNP"
"D33,D36,D39","BZT52C15","Diode_SMD:D_SOD-123","3","DNP"
"D34,D37,D40","SK810L-TP","Diode_SMD:D_SMC","3","DNP"
"D41","BZT52C3V3","Diode_SMD:D_SOD-123","1",""
"F1","250mA 125V 0466.250","Fuse:Fuse_1206_3216Metric","1",""
"F2","20A 58V MINI 0997020.WXN","Fuse:Fuseholder_Blade_Mini_Keystone_3568","1",""
"F3,F4","5A 32V 0466005","Fuse:Fuse_1206_3216Metric","2",""
"F5","2A 32V 0466002","Fuse:Fuse_1206_3216Metric","1",""
"J1","Pack: 8 AWG pigtail pair to an XT90 (mates the pack XT90S), 1 BAT, 2 GND","marengo_revb:SolderWire-8AWG_1x02_P14mm_D4.5mm_OD8mm","1",""
"J3","HS50 A (+X): 1 VBUS, 2 FET drain (Mini-Fit Jr, 18 AWG)","Connector_Molex:Molex_Mini-Fit_Jr_5566-02A_2x01_P4.20mm_Vertical","1",""
"J5","12 V to Jetson (fused, block 10c)","Connector_Molex:Molex_Micro-Fit_3.0_43045-0212_2x01_P3.00mm_Vertical","1",""
"J6","12 V to Pi 5 V buck (fused, block 10c)","Connector_Molex:Molex_Micro-Fit_3.0_43045-0212_2x01_P3.00mm_Vertical","1",""
"J7","12 V to fans (fused, block 10c)","Connector_Molex:Molex_Micro-Fit_3.0_43045-0212_2x01_P3.00mm_Vertical","1",""
"J8","L arm: 16 AWG pigtail pair, 1 +, 2 return","Connector_Wire:SolderWire-2.5sqmm_1x02_P7.2mm_D2.4mm_OD3.6mm","1",""
"J9","R arm: 16 AWG pigtail pair, 1 +, 2 return","Connector_Wire:SolderWire-2.5sqmm_1x02_P7.2mm_D2.4mm_OD3.6mm","1",""
"J10","waist: 16 AWG pigtail pair, 1 +, 2 return","Connector_Wire:SolderWire-2.5sqmm_1x02_P7.2mm_D2.4mm_OD3.6mm","1",""
"J11","aux: 16 AWG pigtail pair, 1 +, 2 return","Connector_Wire:SolderWire-2.5sqmm_1x02_P7.2mm_D2.4mm_OD3.6mm","1","DNP"
"J12","L leg: 14 AWG pigtail pair, 1 +, 2 return","Connector_Wire:SolderWire-2.5sqmm_1x02_P7.2mm_D2.4mm_OD3.6mm","1","DNP"
"J13","R leg: 14 AWG pigtail pair, 1 +, 2 return","Connector_Wire:SolderWire-2.5sqmm_1x02_P7.2mm_D2.4mm_OD3.6mm","1","DNP"
"J20","E-stop: 1 NC out, 2 GND, 3 NC return, 4 GND, 5-6 reset NO, 7 GND, 8 button NO","Connector_JST:JST_GH_SM08B-GHS-TB_1x08-1MP_P1.25mm_Horizontal","1",""
"J21","Pi: 3V3, SDA, GND, SCL, E-stop pressed (low), heartbeat out, port fault (low), power fail (low)","Connector_JST:JST_GH_SM08B-GHS-TB_1x08-1MP_P1.25mm_Horizontal","1",""
"J22","SPARE_SW, off with the motors (2 x 2, keyed apart from the 2-pin outputs)","Connector_Molex:Molex_Micro-Fit_3.0_43045-0412_2x02_P3.00mm_Vertical","1",""
"J23","SPARE_ON, always on","Connector_Molex:Molex_Micro-Fit_3.0_43045-0212_2x01_P3.00mm_Vertical","1",""
"J24","12 V converter pigtail: 1-2 +VIN, 3-4 -VIN, 5 ON/OFF (low = on), 6 -VIN, 7-9 -VOUT, 10-12 +VOUT","Connector_Molex:Molex_Micro-Fit_3.0_43045-1212_2x06_P3.00mm_Vertical","1",""
"J25","HS50 B (-X): 1 VBUS, 2 FET drain (Mini-Fit Jr, 18 AWG)","Connector_Molex:Molex_Mini-Fit_Jr_5566-02A_2x01_P4.20mm_Vertical","1",""
"Q1,Q2,Q7,Q8,Q9,Q15,Q16,Q17","IPB017N10N5LFATMA1","Package_TO_SOT_SMD:TO-263-7_TabPin4","8",""
"Q3","MMBTA92LT1G","Package_TO_SOT_SMD:SOT-23","1",""
"Q4","MMBT3906","Package_TO_SOT_SMD:SOT-23","1",""
"Q5,Q10,Q11,Q14,Q21","MMBT3904","Package_TO_SOT_SMD:SOT-23","5",""
"Q6","BSC040N10NS5ATMA1","Package_TO_SOT_SMD:TDSON-8-1","1",""
"Q12,Q22","2N7002","Package_TO_SOT_SMD:SOT-23","2",""
"Q13","BSC040N10NS5ATMA1","Package_TO_SOT_SMD:TDSON-8-1","1","DNP"
"Q18,Q19,Q20","IPB017N10N5LFATMA1","Package_TO_SOT_SMD:TO-263-7_TabPin4","3","DNP"
"R1,R2,R23,R25,R31,R32","10R","Resistor_SMD:R_0603_1608Metric","6",""
"R3","34k 1%","Resistor_SMD:R_0603_1608Metric","1",""
"R4,R12,R66","1k","Resistor_SMD:R_0603_1608Metric","3",""
"R5,R75,R85,R95,R131","22k","Resistor_SMD:R_0603_1608Metric","5",""
"R6","33k","Resistor_SMD:R_0805_2012Metric","1",""
"R7","464k","Resistor_SMD:R_0603_1608Metric","1",""
"R8","49.9k","Resistor_SMD:R_0603_1608Metric","1",""
"R9","680R 0.5W","Resistor_SMD:R_2010_5025Metric","1",""
"R10","4.7k","Resistor_SMD:R_0603_1608Metric","1",""
"R11,R14,R16,R17,R27,R67,R76,R86,R96,R129","10k","Resistor_SMD:R_0603_1608Metric","10",""
"R13,R24,R28,R37,R38,R41,R50,R65,R71,R72,R77,R81,R82,R87,R91,R92,R97,R130,R137","100k","Resistor_SMD:R_0603_1608Metric","19",""
"R15","1.2k","Resistor_SMD:R_0603_1608Metric","1",""
"R18,R134","9.09k","Resistor_SMD:R_0603_1608Metric","2",""
"R19","499k 0.1%","Resistor_SMD:R_1206_3216Metric","1",""
"R20","604k 0.1%","Resistor_SMD:R_1206_3216Metric","1",""
"R21","51.1k 0.1%","Resistor_SMD:R_0603_1608Metric","1",""
"R22,R64","9.53M","Resistor_SMD:R_0603_1608Metric","2",""
"R26","37.4k 1%","Resistor_SMD:R_0603_1608Metric","1",""
"R29,R68,R78,R88,R138","100R","Resistor_SMD:R_0603_1608Metric","5",""
"R30","1M","Resistor_SMD:R_0603_1608Metric","1",""
"R33,R34","47k 1%","Resistor_SMD:R_1206_3216Metric","2",""
"R35,R73,R83,R93","22R","Resistor_SMD:R_0603_1608Metric","4",""
"R36","40.2k 1%","Resistor_SMD:R_0603_1608Metric","1",""
"R39","68k","Resistor_SMD:R_0603_1608Metric","1",""
"R40","499R 1%","Resistor_SMD:R_0603_1608Metric","1",""
"R42,R47","33k","Resistor_SMD:R_0603_1608Metric","2",""
"R43","1.02k 1%","Resistor_SMD:R_0603_1608Metric","1",""
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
